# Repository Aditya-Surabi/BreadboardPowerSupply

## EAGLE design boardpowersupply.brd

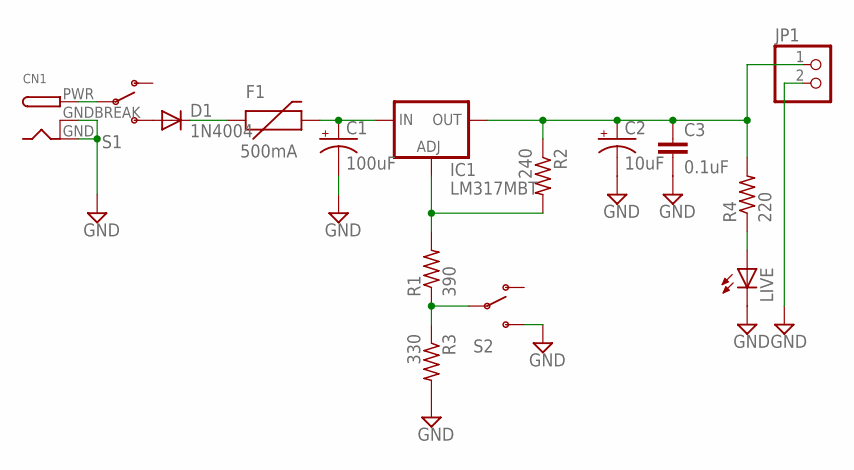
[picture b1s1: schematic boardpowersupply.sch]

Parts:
C1: 100uF; B45181A
C2: 10uF; B45181A
C3: 0.1uF; C2.5-2
CN1: DCBARRELPTH; DCJACK_2MM_PTH
D1: 1N4004; DO41-10
F1: 500mA; PTC
IC1: LM317MBT; TO220L1
JP1: PINHD-1X2; 1X02
LIVE: LED5MM
R1: 390; 0204/7
R2: 240; 0204/7
R3: 330; 0204/7
R4: 220; 0204/7
S1, S2: SWITCH-SPDTKIT; SWITCH-SPDT_KIT

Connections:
GND: C1.-, C2.-, C3.2, CN1.GND, CN1.GNDBREAK, JP1.2, LIVE.K (C), R3.2, S2.3 (S)
unnamed: D1.C, F1.P$1 (1)
unnamed: C1.+, F1.P$2 (2), IC1.3 (IN)
unnamed: D1.A, S1.3 (S)
unnamed: R1.1, R3.1, S2.2
unnamed: IC1.1 (ADJ), R1.2, R2.2
unnamed: LIVE.A, R4.1
unnamed: C2.+, C3.1, IC1.2 (OUT), JP1.1, R2.1, R4.2
unnamed: CN1.PWR, S1.2

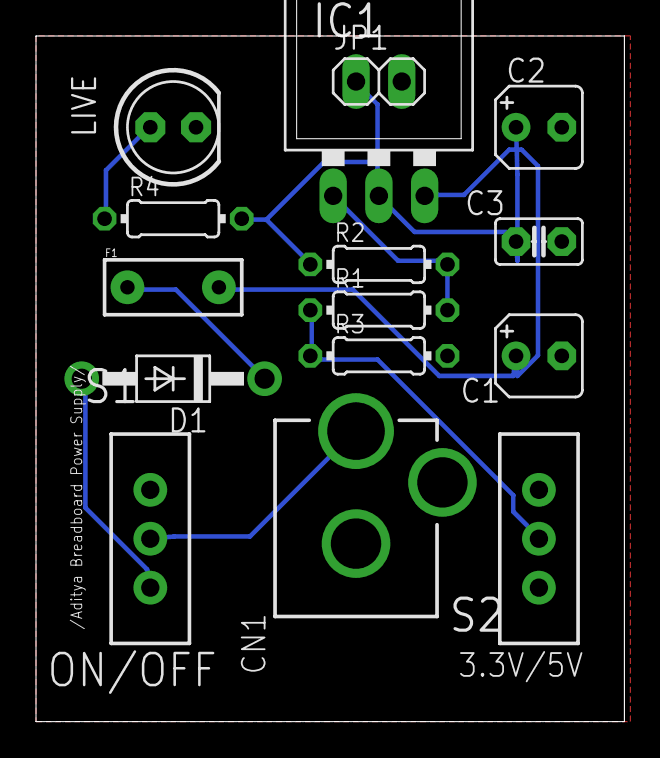
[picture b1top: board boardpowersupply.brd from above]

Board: 2 copper layers, 32.7 x 38.1 mm, 15 parts (0 on the bottom side), 9 nets.

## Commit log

2016-01-18 :tada: Added .gitattributes & .gitignore files
2016-01-18 files
    Schematic and board files.

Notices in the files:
parts and their libraries:
SparkFun-PowerIC: Licensing: Creative Commons ShareAlike 4.0 International - https://creativecommons.org/licenses/by-sa/4.0
